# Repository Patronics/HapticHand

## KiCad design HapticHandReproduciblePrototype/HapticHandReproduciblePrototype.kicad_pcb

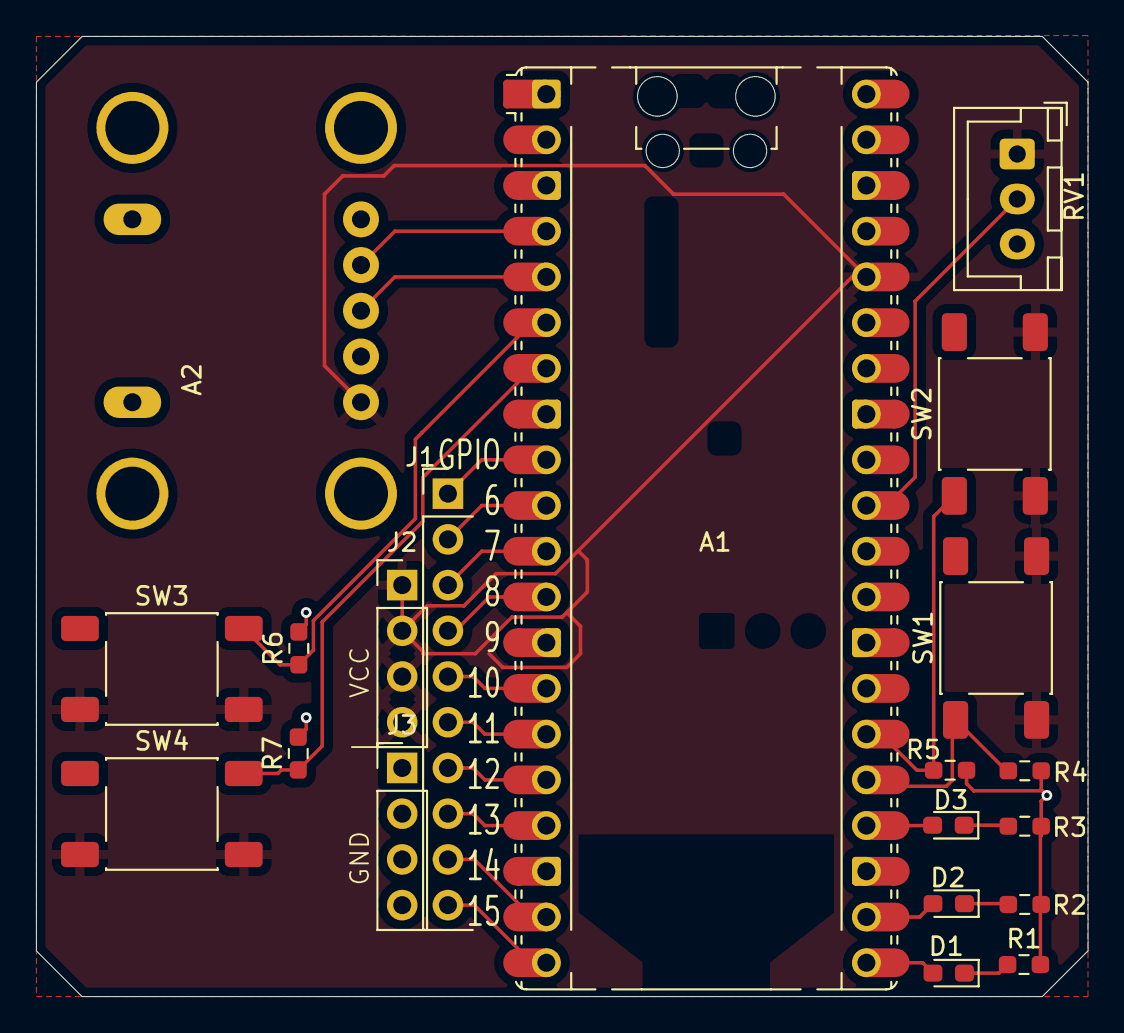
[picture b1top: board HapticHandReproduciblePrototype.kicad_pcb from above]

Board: 2 copper layers, 58.4 x 53.3 mm, 20 parts (0 on the bottom side), 25 nets.

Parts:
A1: RaspberryPi_Pico_W; RaspberryPi_Pico_Common_Unspecified
A2: Haptic Breakout; Adafruit DRV2605L Breakout
D1, D2, D3: LED; LED_0603_1608Metric_Pad1.05x0.95mm_HandSolder
J1: GPIO6-15; PinHeader_1x10_P2.54mm_Vertical
J2, J3: Conn_01x04_Pin; PinHeader_1x04_P2.54mm_Vertical
R1, R2, R3, R4, R5, R6, R7: R_Small; R_0603_1608Metric_Pad0.98x0.95mm_HandSolder
RV1: R_Potentiometer_US; JST_XH_B3B-XH-A_1x03_P2.50mm_Vertical
SW1, SW2, SW3, SW4: SW_Push; SW_Push_1P1T_NO_E-Switch_TL3301NxxxxxG

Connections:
GND: A1.3 (GND), A1.8 (GND), A1.13 (GND), A1.18 (GND), A1.23 (GND), A1.28 (GND), A1.38 (GND), A2.2 (GND), J3.1, J3.2, J3.3, J3.4, R1.2, R2.2, R3.2, R4.2, R5.2, R6.2, R7.2, RV1.3
unnamed: A1.4 (GPIO2), A2.4 (SDA)
unnamed: A1.5 (GPIO3), A2.3 (SCL)
unnamed: A1.9 (GPIO6), J1.1
unnamed: A1.10 (GPIO7), J1.2
unnamed: A1.11 (GPIO8), J1.3
unnamed: A1.12 (GPIO9), J1.4
unnamed: A1.14 (GPIO10), J1.5
unnamed: A1.15 (GPIO11), J1.6
unnamed: A1.16 (GPIO12), J1.7
unnamed: A1.17 (GPIO13), J1.8
unnamed: A1.19 (GPIO14), J1.9
unnamed: A1.20 (GPIO15), J1.10
unnamed: A1.21 (GPIO16), D1.2 (A)
unnamed: A1.22 (GPIO17), D2.2 (A)
unnamed: A1.24 (GPIO18), D3.2 (A)
unnamed: A1.25 (GPIO19), R4.1, SW1.1
unnamed: A1.26 (GPIO20), R5.1, SW2.1
unnamed: A1.31 (GPIO26_ADC0), RV1.2
unnamed: D1.1 (K), R1.1
unnamed: D2.1 (K), R2.1
unnamed: D3.1 (K), R3.1
VCC: A1.36 (3V3), A2.1 (VCC), J2.1, J2.2, J2.3, J2.4, RV1.1, SW1.2, SW2.2, SW3.2, SW4.2
btn_3: A1.6 (GPIO4), R6.1, SW3.1
btn_4: A1.7 (GPIO5), R7.1, SW4.1

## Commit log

2025-10-26 Add hapticHandReproduciblePrototype kidcad project, meant to be a testbed for v2 of the project
